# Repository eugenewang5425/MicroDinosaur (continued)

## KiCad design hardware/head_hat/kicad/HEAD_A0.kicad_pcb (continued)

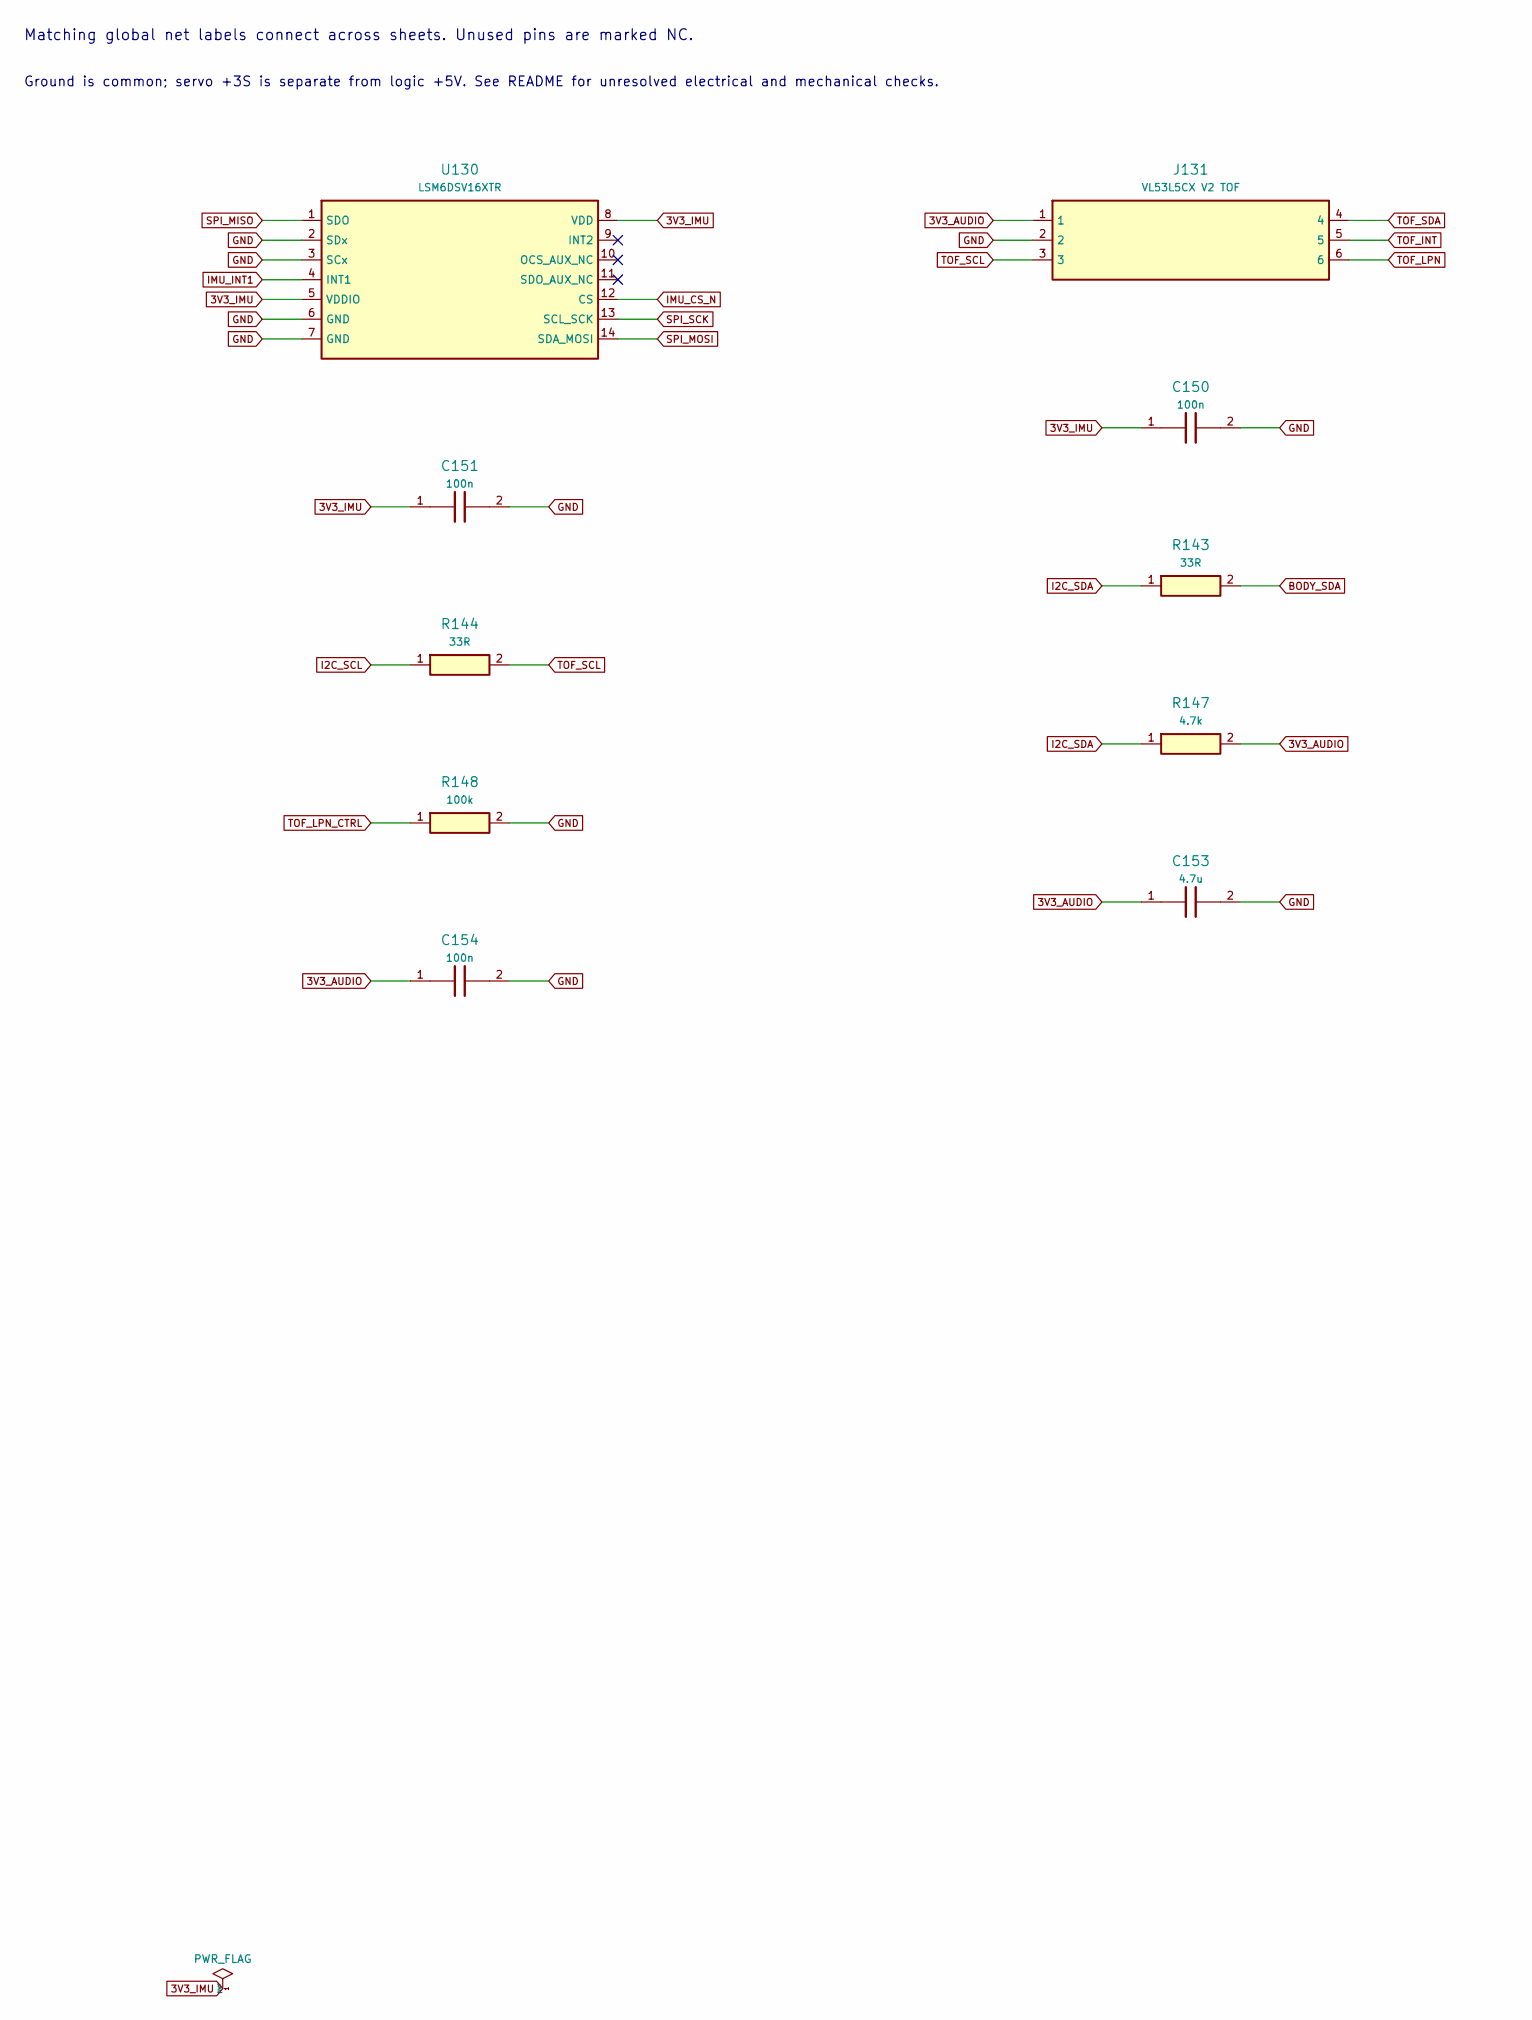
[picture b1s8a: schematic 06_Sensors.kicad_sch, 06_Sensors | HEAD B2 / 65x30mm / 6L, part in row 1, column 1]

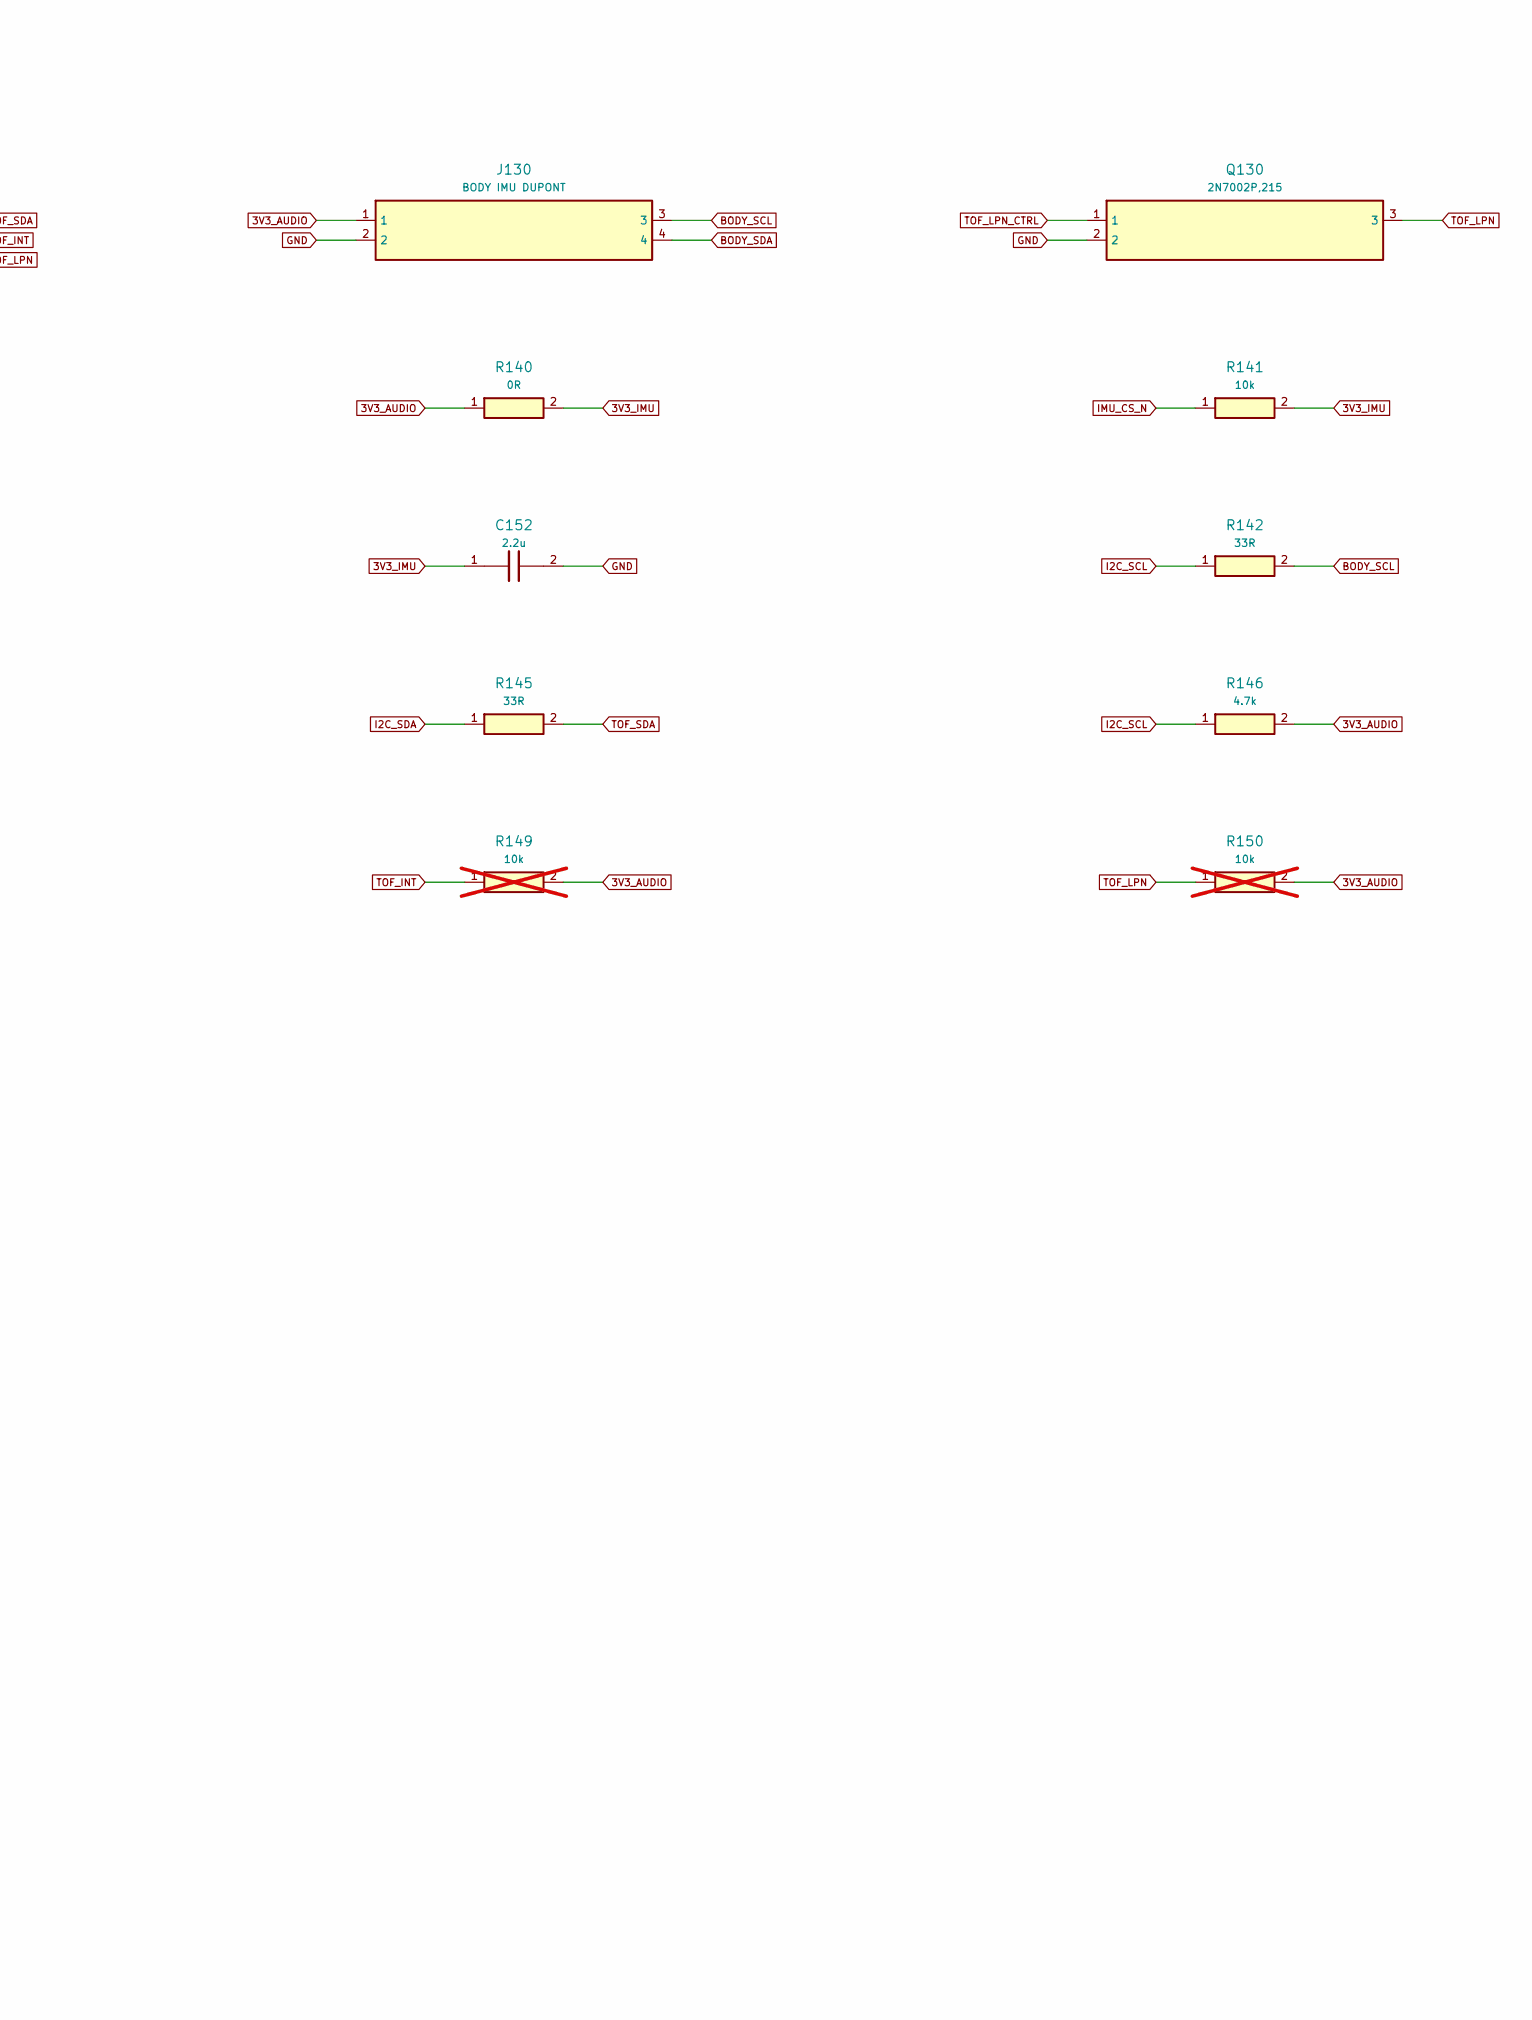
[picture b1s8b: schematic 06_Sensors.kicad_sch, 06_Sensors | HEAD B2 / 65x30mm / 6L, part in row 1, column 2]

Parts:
C150, C151, C154: 100n; Capacitor_SMD__C_0402_1005Metric; MPN GRM155R71C104KA88D
C152: 2.2u; Capacitor_SMD__C_0402_1005Metric; MPN GRM155R60J225ME95D
C153: 4.7u; Capacitor_SMD__C_0603_1608Metric; MPN GRM188R60J475KE19D
J130: BODY IMU DUPONT; Connector_PinHeader_2.54mm__PinHeader_1x04_P2.54mm_Vertical; MPN 61300411121
J131: VL53L5CX V2 TOF; Connector_PinHeader_2.54mm__PinHeader_1x06_P2.54mm_Vertical; MPN 61300611121
Q130: 2N7002P,215; Package_TO_SOT_SMD__SOT-23; MPN 2N7002P,215
R140: 0R; Resistor_SMD__R_0402_1005Metric; MPN RC0402JR-070RL
R141: 10k; Resistor_SMD__R_0402_1005Metric; MPN RC0402FR-0710KL
R142, R143, R144, R145: 33R; Resistor_SMD__R_0402_1005Metric; MPN RC0402FR-0733RL
R146, R147: 4.7k; Resistor_SMD__R_0402_1005Metric; MPN RC0402FR-074K7L
R148: 100k; Resistor_SMD__R_0402_1005Metric; MPN RC0402FR-07100KL
R149, R150: 10k; Resistor_SMD__R_0402_1005Metric; MPN RC0402FR-0710KL; not fitted
U130: LSM6DSV16XTR; Package_LGA__LGA-14_3x2.5mm_P0.5mm_LayoutBorder3x4y; MPN LSM6DSV16XTR

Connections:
3V3_AUDIO: C153.1, C154.1, J130.1, J131.1, R140.1, R146.2, R147.2, R149.2, R150.2; also elsewhere on the board
3V3_IMU: C150.1, C151.1, C152.1, R140.2, R141.2, U130.5 (VDDIO), U130.8 (VDD)
BODY_SCL: J130.3, R142.2
BODY_SDA: J130.4, R143.2
GND: C150.2, C151.2, C152.2, C153.2, C154.2, J130.2, J131.2, Q130.2, R148.2, U130.2 (SDx), U130.3 (SCx), U130.6 (GND), U130.7 (GND); also elsewhere on the board
I2C_SCL: R142.1, R144.1, R146.1; also elsewhere on the board
I2C_SDA: R143.1, R145.1, R147.1; also elsewhere on the board
IMU_CS_N: R141.1, U130.12 (CS); also elsewhere on the board
IMU_INT1: U130.4 (INT1); also elsewhere on the board
SPI_MISO: U130.1 (SDO); also elsewhere on the board
SPI_MOSI: U130.14 (SDA_MOSI); also elsewhere on the board
SPI_SCK: U130.13 (SCL_SCK); also elsewhere on the board
TOF_INT: J131.5, R149.1; also elsewhere on the board
TOF_LPN: J131.6, Q130.3, R150.1
TOF_LPN_CTRL: Q130.1, R148.1; also elsewhere on the board
TOF_SCL: J131.3, R144.2
TOF_SDA: J131.4, R145.2

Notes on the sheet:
Matching global net labels connect across sheets. Unused pins are marked NC.
Ground is common; servo +3S is separate from logic +5V. See README for unresolved electrical and mechanical checks.

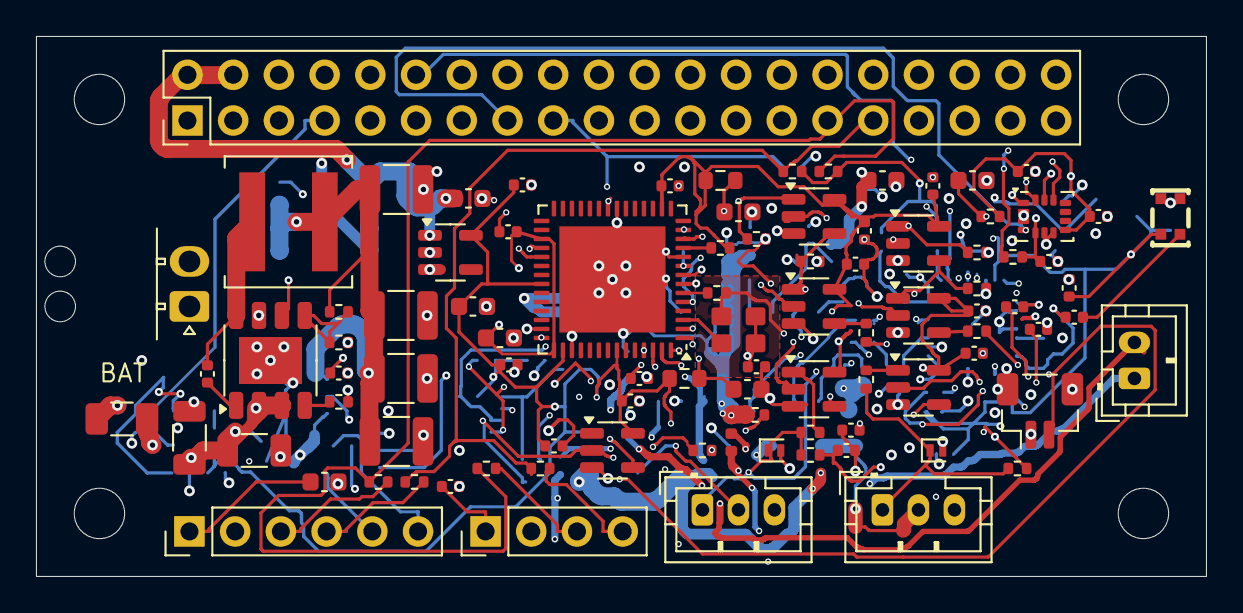
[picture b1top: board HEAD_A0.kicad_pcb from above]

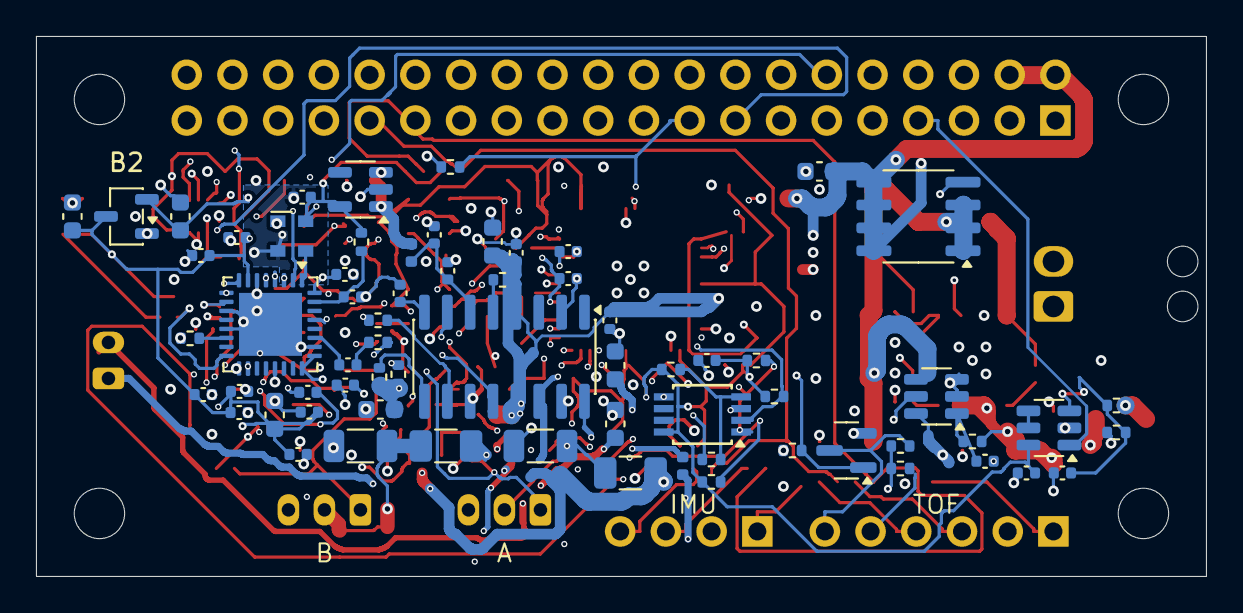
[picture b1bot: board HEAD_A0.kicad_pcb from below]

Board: 6 copper layers, 65.0 x 30.0 mm, 163 parts (67 on the bottom side), 91 nets.

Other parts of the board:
H1, H2, H3, H4: 2.8mm M2.5; MountingHole_2.7mm_M2.5

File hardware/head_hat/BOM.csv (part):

Reference,Value,MPN,Footprint,Side,Fit,Function,Note,Source
U1,PAM8406D,PAM8406DR,HEAD:Pollen_U1,B,YES,02_Audio_Amplifier,Pollen D1 audio connection retained. Left amplifier outputs unused; one external mic connector retained.,Pollen 6de86283297e4c49a9da8312cd3395ab83c437e3
U2,TLV320AIC3104IRHBR,TLV320AIC3104IRHBR,HEAD:Pollen_U2,B,YES,02_Audio_Codec,Pollen D1 audio connection retained. Left amplifier outputs unused; one external mic connector retained.,Pollen 6de86283297e4c49a9da8312cd3395ab83c437e3
U3,XC6206P182MR,XC6206P182MR-G,HEAD:Pollen_U3,B,YES,02_Audio_Codec,Pollen D1 audio connection retained. Left amplifier outputs unused; one external mic connector retained.,Pollen 6de86283297e4c49a9da8312cd3395ab83c437e3
Y1,12MHz CMOS 3.3V,ASDMB-12.000MHZ-LC-T,HEAD:Pollen_Y1,B,YES,02_Audio_Codec,Pollen D1 audio connection retained. Left amplifier outputs unused; one external mic connector retained.,Pollen 6de86283297e4c49a9da8312cd3395ab83c437e3
MK1,Microphone_MEMS,LMA2718T421-OA5-2,HEAD:Pollen_MK1,F,YES,02_Audio_Codec,Pollen D1 audio connection retained. Left amplifier outputs unused; one external mic connector retained.,Pollen 6de86283297e4c49a9da8312cd3395ab83c437e3
FB1,300mA 600R@100MHz,BLM15AG601SN1D,HEAD:Pollen_FB1,B,YES,02_Audio_Amplifier,Pollen D1 audio connection retained. Left amplifier outputs unused; one external mic connector retained. B1: manufacturer rating 300mA; Pollen 1.3A text was incorrect. Amplifier VDD current budget remains to be verified.,Pollen 6de86283297e4c49a9da8312cd3395ab83c437e3
FB2,2A - 120R@100MHz,BLM15PX121SN1D,HEAD:Pollen_FB2,F,YES,02_Audio_Amplifier,"Pollen D1 audio connection retained. Left amplifier outputs unused; one external mic connector retained. B1: corrected to 0402 2A 120ohm; original custom footprint is 0402, not 0603.",Pollen 6de86283297e4c49a9da8312cd3395ab83c437e3
FB3,2A - 120R@100MHz,BLM15PX121SN1D,HEAD:Pollen_FB3,B,YES,02_Audio_Amplifier,"Pollen D1 audio connection retained. Left amplifier outputs unused; one external mic connector retained. B1: corrected to 0402 2A 120ohm; original custom footprint is 0402, not 0603.",Pollen 6de86283297e4c49a9da8312cd3395ab83c437e3
C1,1u,GRM155R61A105KE15D,Capacitor_SMD:C_0402_1005Metric,B,YES,02_Audio_Amplifier,Pollen D1 audio connection retained. Left amplifier outputs unused; one external mic connector retained.,Pollen 6de86283297e4c49a9da8312cd3395ab83c437e3
C2,1u,GRM155R61A105KE15D,Capacitor_SMD:C_0402_1005Metric,B,YES,02_Audio_Amplifier,Pollen D1 audio connection retained. Left amplifier outputs unused; one external mic connector retained.,Pollen 6de86283297e4c49a9da8312cd3395ab83c437e3
C3,1u,GRM155R61A105KE15D,Capacitor_SMD:C_0402_1005Metric,B,YES,02_Audio_Amplifier,Pollen D1 audio connection retained. Left amplifier outputs unused; one external mic connector retained.,Pollen 6de86283297e4c49a9da8312cd3395ab83c437e3
C4,1u,GRM155R61A105KE15D,Capacitor_SMD:C_0402_1005Metric,B,YES,02_Audio_Amplifier,Pollen D1 audio connection retained. Left amplifier outputs unused; one external mic connector retained.,Pollen 6de86283297e4c49a9da8312cd3395ab83c437e3
C5,10u,GRM188R61A106KE69D,Capacitor_SMD:C_0603_1608Metric,B,YES,02_Audio_Amplifier,Pollen D1 audio connection retained. Left amplifier outputs unused; one external mic connector retained.,Pollen 6de86283297e4c49a9da8312cd3395ab83c437e3
C6,1u,GRM155R61A105KE15D,Capacitor_SMD:C_0402_1005Metric,B,YES,02_Audio_Amplifier,Pollen D1 audio connection retained. Left amplifier outputs unused; one external mic connector retained.,Pollen 6de86283297e4c49a9da8312cd3395ab83c437e3
C7,10u,GRM188R61A106KE69D,Capacitor_SMD:C_0603_1608Metric,B,YES,02_Audio_Amplifier,Pollen D1 audio connection retained. Left amplifier outputs unused; one external mic connector retained.,Pollen 6de86283297e4c49a9da8312cd3395ab83c437e3
C8,220p,GRM1885C1H221JA01D,Capacitor_SMD:C_0603_1608Metric,B,YES,02_Audio_Amplifier,Pollen D1 audio connection retained. Left amplifier outputs unused; one external mic connector retained.,Pollen 6de86283297e4c49a9da8312cd3395ab83c437e3
C9,220p,GRM1885C1H221JA01D,Capacitor_SMD:C_0603_1608Metric,B,YES,02_Audio_Amplifier,Pollen D1 audio connection retained. Left amplifier outputs unused; one external mic connector retained.,Pollen 6de86283297e4c49a9da8312cd3395ab83c437e3
C10,1u,GRM155R61A105KE15D,Capacitor_SMD:C_0402_1005Metric,F,YES,02_Audio_Codec,Pollen D1 audio connection retained. Left amplifier outputs unused; one external mic connector retained.,Pollen 6de86283297e4c49a9da8312cd3395ab83c437e3
C11,100n,GRM155R71C104KA88D,Capacitor_SMD:C_0402_1005Metric,F,YES,02_Audio_Codec,Pollen D1 audio connection retained. Left amplifier outputs unused; one external mic connector retained.,Pollen 6de86283297e4c49a9da8312cd3395ab83c437e3
C12,10u,GRM188R61A106KE69D,Capacitor_SMD:C_0603_1608Metric,B,YES,02_Audio_Codec,Pollen D1 audio connection retained. Left amplifier outputs unused; one external mic connector retained.,Pollen 6de86283297e4c49a9da8312cd3395ab83c437e3
C13,10u,GRM188R61A106KE69D,Capacitor_SMD:C_0603_1608Metric,B,YES,02_Audio_Codec,Pollen D1 audio connection retained. Left amplifier outputs unused; one external mic connector retained.,Pollen 6de86283297e4c49a9da8312cd3395ab83c437e3
C14,100n,GRM155R71C104KA88D,Capacitor_SMD:C_0402_1005Metric,B,YES,02_Audio_Codec,Pollen D1 audio connection retained. Left amplifier outputs unused; one external mic connector retained.,Pollen 6de86283297e4c49a9da8312cd3395ab83c437e3
C26,100n,GRM155R71C104KA88D,Capacitor_SMD:C_0402_1005Metric,B,YES,02_Audio_Codec,Pollen D1 audio connection retained. Left amplifier outputs unused; one external mic connector retained.,Pollen 6de86283297e4c49a9da8312cd3395ab83c437e3
C27,1u,GRM155R61A105KE15D,Capacitor_SMD:C_0402_1005Metric,B,YES,02_Audio_Codec,Pollen D1 audio connection retained. Left amplifier outputs unused; one external mic connector retained.,Pollen 6de86283297e4c49a9da8312cd3395ab83c437e3
C28,100n,GRM155R71C104KA88D,Capacitor_SMD:C_0402_1005Metric,B,YES,02_Audio_Codec,Pollen D1 audio connection retained. Left amplifier outputs unused; one external mic connector retained.,Pollen 6de86283297e4c49a9da8312cd3395ab83c437e3
C29,1u,GRM155R61A105KE15D,Capacitor_SMD:C_0402_1005Metric,B,YES,02_Audio_Codec,Pollen D1 audio connection retained. Left amplifier outputs unused; one external mic connector retained.,Pollen 6de86283297e4c49a9da8312cd3395ab83c437e3
C30,100n,GRM155R71C104KA88D,Capacitor_SMD:C_0402_1005Metric,B,YES,02_Audio_Codec,Pollen D1 audio connection retained. Left amplifier outputs unused; one external mic connector retained.,Pollen 6de86283297e4c49a9da8312cd3395ab83c437e3
C31,1u,GRM155R61A105KE15D,Capacitor_SMD:C_0402_1005Metric,B,YES,02_Audio_Codec,Pollen D1 audio connection retained. Left amplifier outputs unused; one external mic connector retained.,Pollen 6de86283297e4c49a9da8312cd3395ab83c437e3
C32,100n,GRM155R71C104KA88D,Capacitor_SMD:C_0402_1005Metric,B,YES,02_Audio_Codec,Pollen D1 audio connection retained. Left amplifier outputs unused; one external mic connector retained.,Pollen 6de86283297e4c49a9da8312cd3395ab83c437e3
C33,1u,GRM155R61A105KE15D,Capacitor_SMD:C_0402_1005Metric,B,YES,02_Audio_Amplifier,Pollen D1 audio connection retained. Left amplifier outputs unused; one external mic connector retained.,Pollen 6de86283297e4c49a9da8312cd3395ab83c437e3
C34,10n,GRM155R71H103KA88D,Capacitor_SMD:C_0402_1005Metric,B,YES,02_Audio_Amplifier,Pollen D1 audio connection retained. Left amplifier outputs unused; one external mic connector retained.,Pollen 6de86283297e4c49a9da8312cd3395ab83c437e3
C35,1u,GRM155R61A105KE15D,Capacitor_SMD:C_0402_1005Metric,B,YES,02_Audio_Codec,Pollen D1 audio connection retained. Left amplifier outputs unused; one external mic connector retained.,Pollen 6de86283297e4c49a9da8312cd3395ab83c437e3
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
